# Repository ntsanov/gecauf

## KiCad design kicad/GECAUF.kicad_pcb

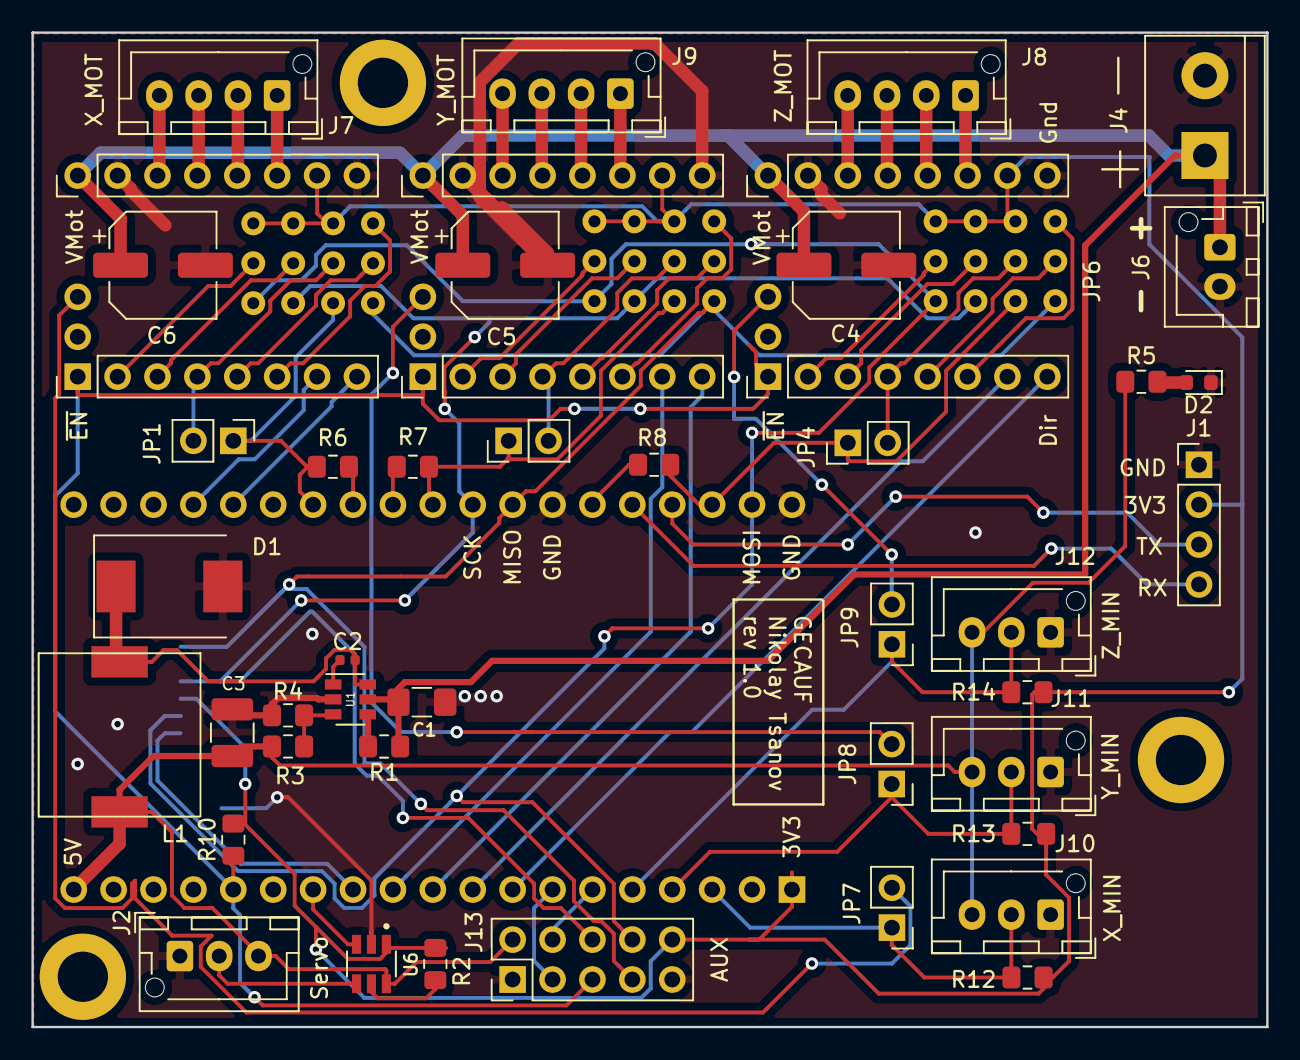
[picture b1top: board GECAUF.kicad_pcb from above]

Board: 2 copper layers, 78.6 x 63.3 mm, 48 parts (1 on the bottom side), 66 nets.

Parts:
C1: 35V/4.7uF; C_1206_3216Metric_Pad1.42x1.75mm_HandSolder
C2: 0.1uF/16V; C_0402_1005Metric
C3: 16v/10uF; C_1210_3225Metric_Pad1.42x2.65mm_HandSolder
C4, C5, C6: 35V/100uF; CP_Elec_6.3x7.7
D1: B340; D_SMC
D2: LED; LED_0603_1608Metric
J1: Uart; PinHeader_1x04_P2.54mm_Vertical
J2: Servo; JST_XH_B3B-XH-AM_1x03_P2.50mm_Vertical
J4: Power; TerminalBlock_bornier-2_P5.08mm
J5: microSD; MOLEX-472192001
J6: Power out; JST_XH_B2B-XH-AM_1x02_P2.50mm_Vertical
J7: X_MOT; JST_XH_B4B-XH-AM_1x04_P2.50mm_Vertical
J8: Z_MOT; JST_XH_B4B-XH-AM_1x04_P2.50mm_Vertical
J9: Y_MOT; JST_XH_B4B-XH-AM_1x04_P2.50mm_Vertical
J10: X_MIN; JST_XH_B3B-XH-AM_1x03_P2.50mm_Vertical
J11: Y_MIN; JST_XH_B3B-XH-AM_1x03_P2.50mm_Vertical
J12: Z_MIN; JST_XH_B3B-XH-AM_1x03_P2.50mm_Vertical
J13: AUX; PinHeader_2x05_P2.54mm_Vertical
JP1, JP3, JP4, JP7, JP8, JP9: Jumper; PinHeader_1x02_P2.54mm_Vertical
JP2: X_CFG; cfg_pins
JP5: Y_CFG; cfg_pins
JP6: Z_CFG; cfg_pins
L1: 22uH; SMDRH104R
R1: 49.9k; R_0805_2012Metric_Pad1.15x1.40mm_HandSolder
R2, R12, R13, R14: 10k; R_0805_2012Metric_Pad1.15x1.40mm_HandSolder
R3: 49,9k; R_0805_2012Metric_Pad1.15x1.40mm_HandSolder
R4: 9.53k; R_0805_2012Metric_Pad1.15x1.40mm_HandSolder
R5: 2k; R_0805_2012Metric_Pad1.15x1.40mm_HandSolder
R6, R7, R8: 1K; R_0805_2012Metric_Pad1.15x1.40mm_HandSolder
R10: 10K; R_0805_2012Metric_Pad1.15x1.40mm_HandSolder
U1: AOZ1282CI; SOT-23-6
U2: esp32-dev
U3, U4, U5: stepstick
U6: TXS0101DBVR; SOT95P280X145-6N

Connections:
+3V3: J1.2, J5.4, J13.10, JP2.4, JP2.7, JP2.10, JP5.4, JP5.7, JP5.10, JP6.4, JP6.7, JP6.10, R2.1, R10.2, R12.2, R13.2, R14.2, U2.1, U3.15, U4.15, U5.15, U6.1
+5V: C3.1, J2.3, J10.3, J11.3, J12.3, J13.2, L1.2, R3.2, R5.1, U2.19, U6.6
AUX1: J13.3, U2.7
AUX2: J13.4, U2.6
Earth: C1.2, C3.2, C4.2, C5.2, C6.2, D1.2, D2.1, J1.1, J2.1, J4.2, J5.G1, J5.G2, J5.G3, J5.G4, J6.2, J10.1, J11.1, J12.1, J13.1, J13.9, R4.2, U1.2, U2.20, U2.26, U3.10, U3.16, U4.10, U4.16, U5.10, U5.16, U6.2
Enable: J13.5, R10.1, U2.15, U3.1, U4.1, U5.1
unnamed: C2.1, U1.1
unnamed: C2.2, D1.1, L1.1, U1.6
unnamed: D2.2, R5.2
unnamed: J7.1, U3.14
unnamed: J7.2, U3.13
unnamed: J7.3, U3.12
unnamed: J7.4, U3.11
unnamed: J8.1, U5.14
unnamed: J8.2, U5.13
unnamed: J8.3, U5.12
unnamed: J8.4, U5.11
unnamed: J9.1, U4.14
unnamed: J9.2, U4.13
unnamed: J9.3, U4.12
unnamed: J9.4, U4.11
unnamed: JP1.2, JP2.5, U3.4
unnamed: JP2.1, U3.6
unnamed: JP2.2, U3.5
unnamed: JP2.8, U3.3
unnamed: JP2.11, U3.2
unnamed: JP3.2, JP5.5, U4.4
unnamed: JP4.2, JP6.5, U5.4
unnamed: JP5.1, U4.6
unnamed: JP5.2, U4.5
unnamed: JP5.8, U4.3
unnamed: JP5.11, U4.2
unnamed: JP6.1, U5.6
unnamed: JP6.2, U5.5
unnamed: JP6.8, U5.3
unnamed: JP6.11, U5.2
unnamed: JP7.2, U3.18
unnamed: JP8.2, U4.18
unnamed: JP9.2, U5.18
unnamed: R1.2, U1.4
unnamed: R2.2, U6.5
unnamed: R3.1, R4.1, U1.3
RX: J1.4, U2.24
SD_CS: J5.2, U2.12
SPI_MISO: J5.7, J13.7, JP2.3, JP5.3, JP6.3, U2.27
SPI_MOSI: J5.3, J13.8, JP2.12, JP5.12, JP6.12, U2.21
SPI_SCK: J5.5, J13.6, JP2.9, JP5.9, JP6.9, U2.28
Servo_PWM_3v3: U2.13, U6.3
Servo_PWM_5V: J2.2, U6.4
TX: J1.3, U2.23
Vin: C1.1, C4.1, C5.1, C6.1, J4.1, J6.1, R1.1, U1.5, U3.9, U4.9, U5.9
X_CS: JP1.1, JP2.6, R6.1, U2.32
X_DIR: U2.34, U3.8
X_MIN: J10.2, JP7.1, R12.1, U2.3
X_STEP: U2.35, U3.7
X_TX: R6.2, U2.31
Y_CS: JP3.1, JP5.6, R7.1, U2.29
Y_DIR: U2.10, U4.8
Y_MIN: J11.2, JP8.1, R13.1, U2.4
Y_STEP: U2.11, U4.7
Y_TX: R7.2, U2.30
Z_CS: JP4.1, JP6.6, R8.1, U2.22
Z_DIR: U2.8, U5.8
Z_MIN: J12.2, JP9.1, R14.1, U2.5
Z_STEP: U2.9, U5.7
Z_TX: R8.2, U2.25

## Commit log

2022-06-22 Basic pen plotter config
